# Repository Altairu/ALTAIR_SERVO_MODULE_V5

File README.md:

# ALTAIR_SERVO_MODULE_V5
ALTAIR_SERVO_MODULE_V5

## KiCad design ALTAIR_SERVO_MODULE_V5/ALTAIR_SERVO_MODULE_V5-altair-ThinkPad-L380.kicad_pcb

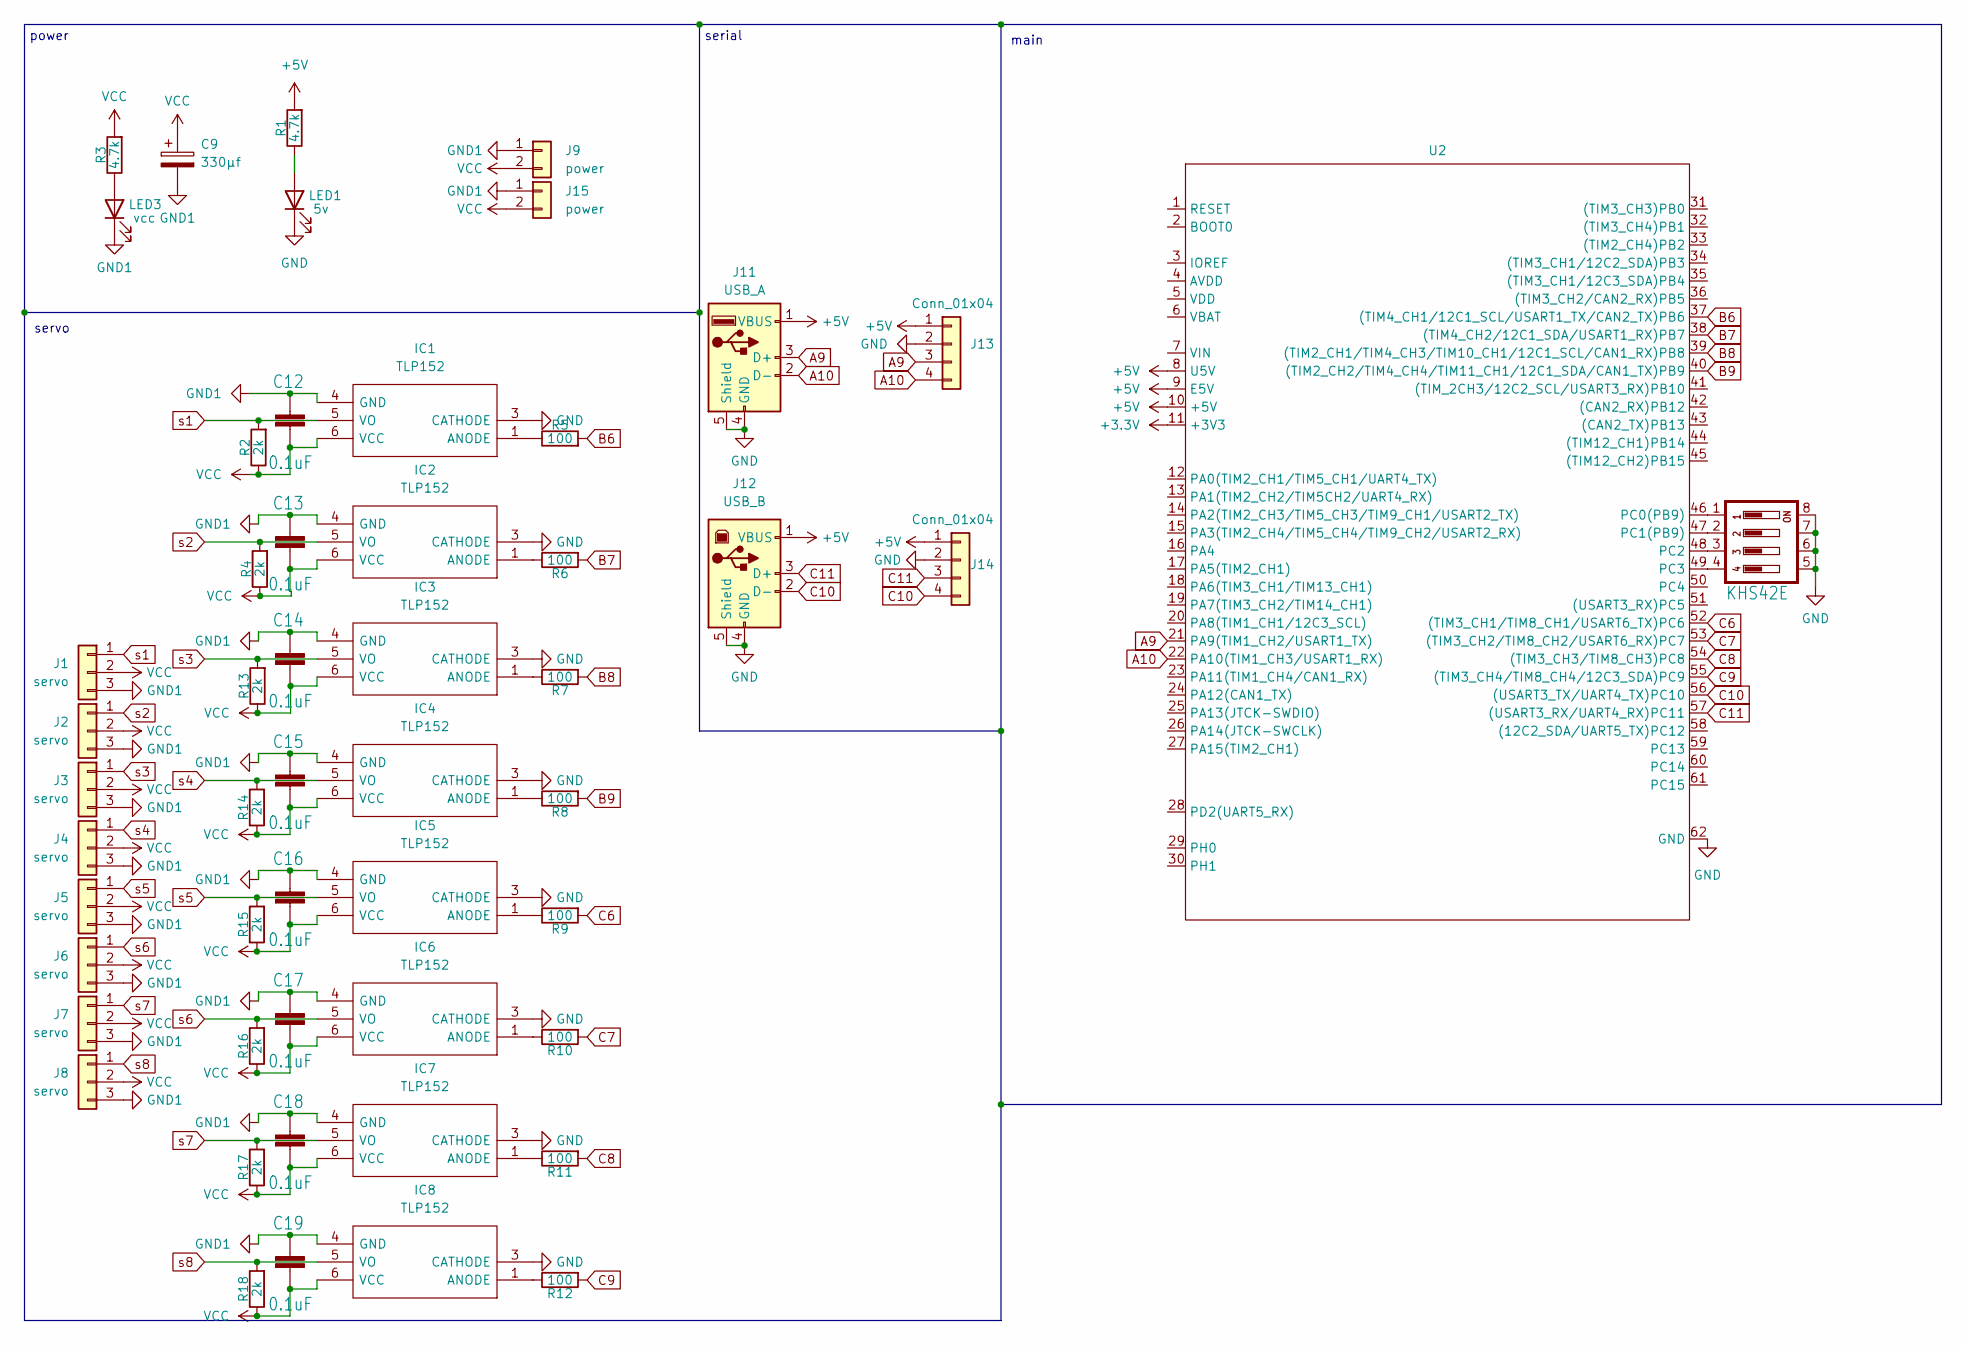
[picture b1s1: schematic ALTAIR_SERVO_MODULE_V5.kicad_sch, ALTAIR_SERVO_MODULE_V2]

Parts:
C9: 330μf; CP_Elec_10x10
C12, C13, C14, C15, C16, C17, C18, C19: 0.1uF; C_0603_1608Metric
IC1, IC2, IC3, IC4, IC5, IC6, IC7, IC8: TLP152; 11-4L1S_5-PIN-SOIC_; Manufacturer_Part_Number TLP152; Mouser Part Number N/A
J1, J2, J3, J4, J5, J6, J7, J8: servo; JST_XA_S03B-XASK-1_1x03_P2.50mm_Horizontal
J9, J15: power; AMASS_XT60PW-M_1x02_P7.20mm_Horizontal
J11: USB_A; USB_A_Molex_67643_Horizontal
J12: USB_B; USB_B_Lumberg_2411_02_Horizontal
J13, J14: Conn_01x04; JST_XA_B04B-XASK-1_1x04_P2.50mm_Vertical
LED1: 5v; LED_0603_1608Metric
LED3: vcc; LED_0603_1608Metric
R1, R3: 4.7k; R_0603_1608Metric
R2, R4, R13, R14, R15, R16, R17, R18: 2k; R_0603_1608Metric
R5, R6, R7, R8, R9, R10, R11, R12: 100; R_0603_1608Metric
S2: KHS42E; SOIC127P600X175-8N
U2: STM32F446RE_Nucleo

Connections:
+3.3V: U2.11 (+3V3)
+5V: J11.1 (VBUS), J12.1 (VBUS), J13.1, J14.1, R1.2, U2.8 (U5V), U2.9 (E5V), U2.10 (+5V)
A9: J11.3 (D+), J13.3, U2.21 (PA9(TIM1_CH2/USART1_TX))
A10: J11.2 (D-), J13.4, U2.22 (PA10(TIM1_CH3/USART1_RX))
B6: R5.2, U2.37 ((TIM4_CH1/12C1_SCL/USART1_TX/CAN2_TX)PB6)
B7: R6.2, U2.38 ((TIM4_CH2/12C1_SDA/USART1_RX)PB7)
B8: R7.2, U2.39 ((TIM2_CH1/TIM4_CH3/TIM10_CH1/12C1_SCL/C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)
B9: R8.2, U2.40 ((TIM2_CH2/TIM4_CH4/TIM11_CH1/12C1_SDA/C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)
C6: R9.2, U2.52 ((TIM3_CH1/TIM8_CH1/USART6_TX)PC6)
C7: R10.2, U2.53 ((TIM3_CH2/TIM8_CH2/USART6_RX)PC7)
C8: R11.2, U2.54 ((TIM3_CH3/TIM8_CH3)PC8)
C9: R12.2, U2.55 ((TIM3_CH4/TIM8_CH4/12C3_SDA)PC9)
C10: J12.2 (D-), J14.4, U2.56 ((USART3_TX/UART4_TX)PC10)
C11: J12.3 (D+), J14.3, U2.57 ((USART3_RX/UART4_RX)PC11)
GND: IC1.3 (CATHODE), IC2.3 (CATHODE), IC3.3 (CATHODE), IC4.3 (CATHODE), IC5.3 (CATHODE), IC6.3 (CATHODE), IC7.3 (CATHODE), IC8.3 (CATHODE), J11.4 (GND), J11.5 (Shield), J12.4 (GND), J12.5 (Shield), J13.2, J14.2, LED1.1 (K), S2.5, S2.6, S2.7, S2.8, U2.62 (GND)
GND1: C9.2, C12.1, C13.1, C14.1, C15.1, C16.1, C17.1, C18.1, C19.1, IC1.4 (GND), IC2.4 (GND), IC3.4 (GND), IC4.4 (GND), IC5.4 (GND), IC6.4 (GND), IC7.4 (GND), IC8.4 (GND), J1.3, J2.3, J3.3, J4.3, J5.3, J6.3, J7.3, J8.3, J9.1, J15.1, LED3.1 (K)
unnamed: IC1.1 (ANODE), R5.1
unnamed: IC2.1 (ANODE), R6.1
unnamed: IC3.1 (ANODE), R7.1
unnamed: IC4.1 (ANODE), R8.1
unnamed: IC5.1 (ANODE), R9.1
unnamed: IC6.1 (ANODE), R10.1
unnamed: IC7.1 (ANODE), R11.1
unnamed: IC8.1 (ANODE), R12.1
unnamed: LED1.2 (A), R1.1
unnamed: LED3.2 (A), R3.1
unnamed: S2.1, U2.46 (PC0(PB9))
unnamed: S2.2, U2.47 (PC1(PB9))
unnamed: S2.3, U2.48 (PC2)
unnamed: S2.4, U2.49 (PC3)
VCC: C9.1, C12.2, C13.2, C14.2, C15.2, C16.2, C17.2, C18.2, C19.2, IC1.6 (VCC), IC2.6 (VCC), IC3.6 (VCC), IC4.6 (VCC), IC5.6 (VCC), IC6.6 (VCC), IC7.6 (VCC), IC8.6 (VCC), J1.2, J2.2, J3.2, J4.2, J5.2, J6.2, J7.2, J8.2, J9.2, J15.2, R2.1, R3.2, R4.1, R13.1, R14.1, R15.1, R16.1, R17.1, R18.1
s1: IC1.5 (VO), J1.1, R2.2
s2: IC2.5 (VO), J2.1, R4.2
s3: IC3.5 (VO), J3.1, R13.2
s4: IC4.5 (VO), J4.1, R14.2
s5: IC5.5 (VO), J5.1, R15.2
s6: IC6.5 (VO), J6.1, R16.2
s7: IC7.5 (VO), J7.1, R17.2
s8: IC8.5 (VO), J8.1, R18.2

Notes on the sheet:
serial
main
power
servo

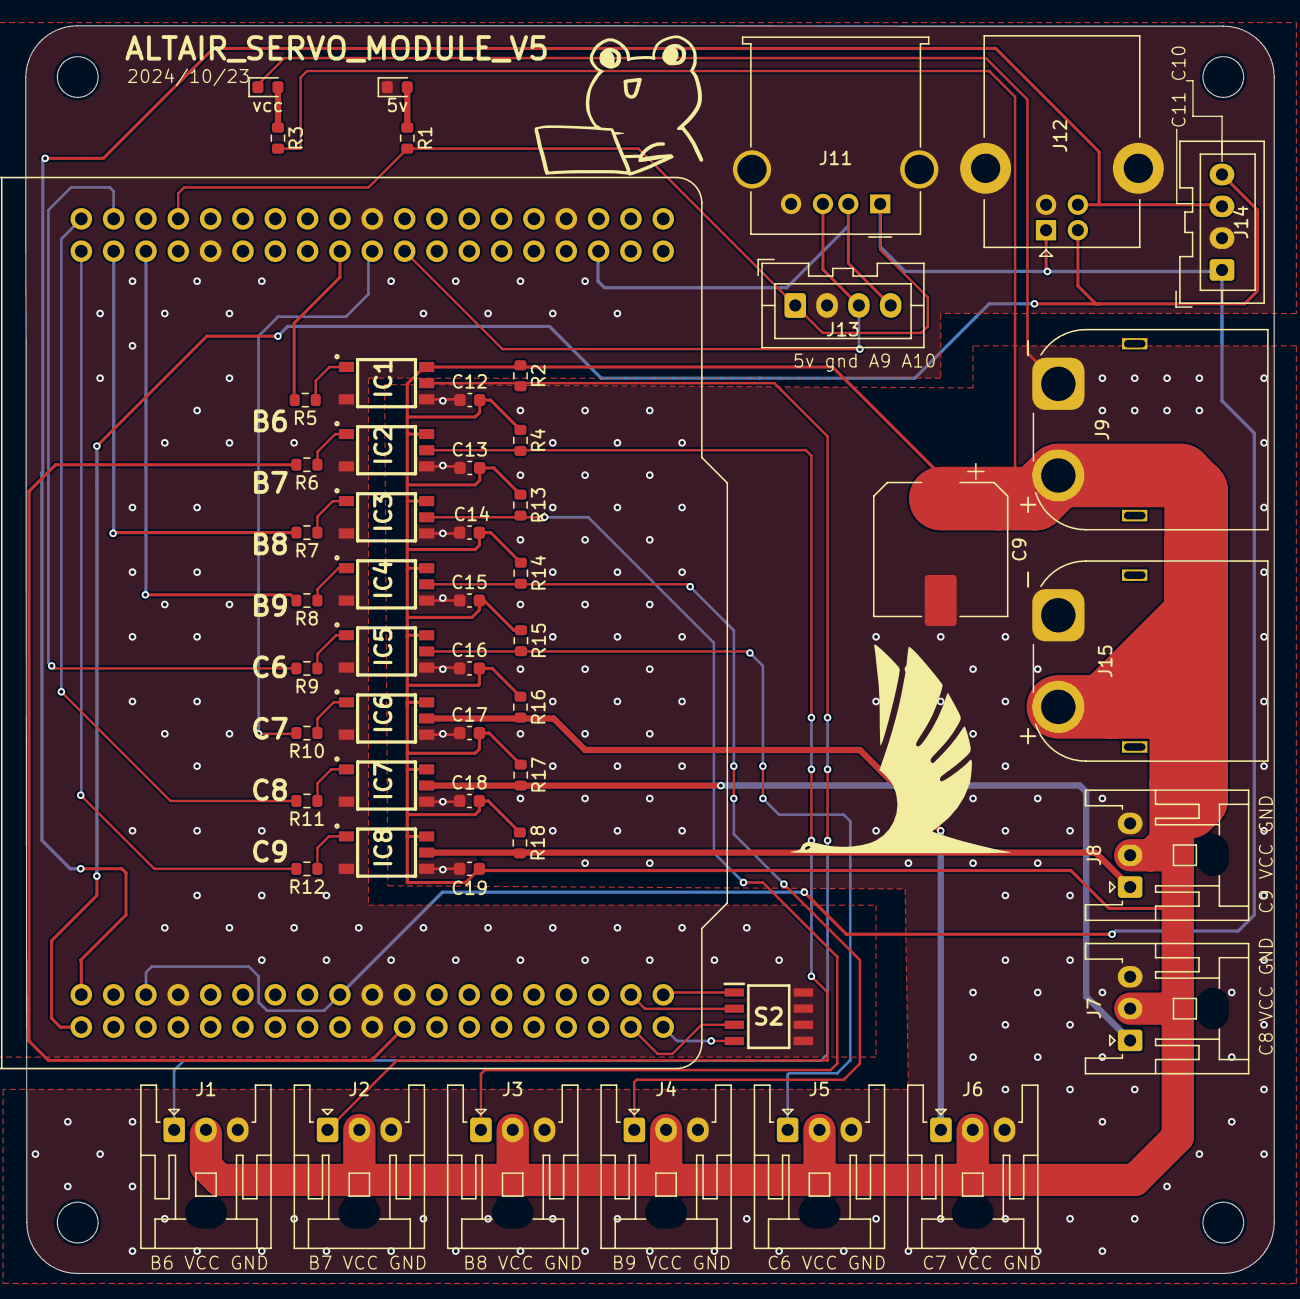
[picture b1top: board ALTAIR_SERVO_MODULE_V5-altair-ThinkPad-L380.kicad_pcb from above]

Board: 2 copper layers, 98.1 x 98.0 mm, 53 parts (0 on the bottom side), 38 nets.
